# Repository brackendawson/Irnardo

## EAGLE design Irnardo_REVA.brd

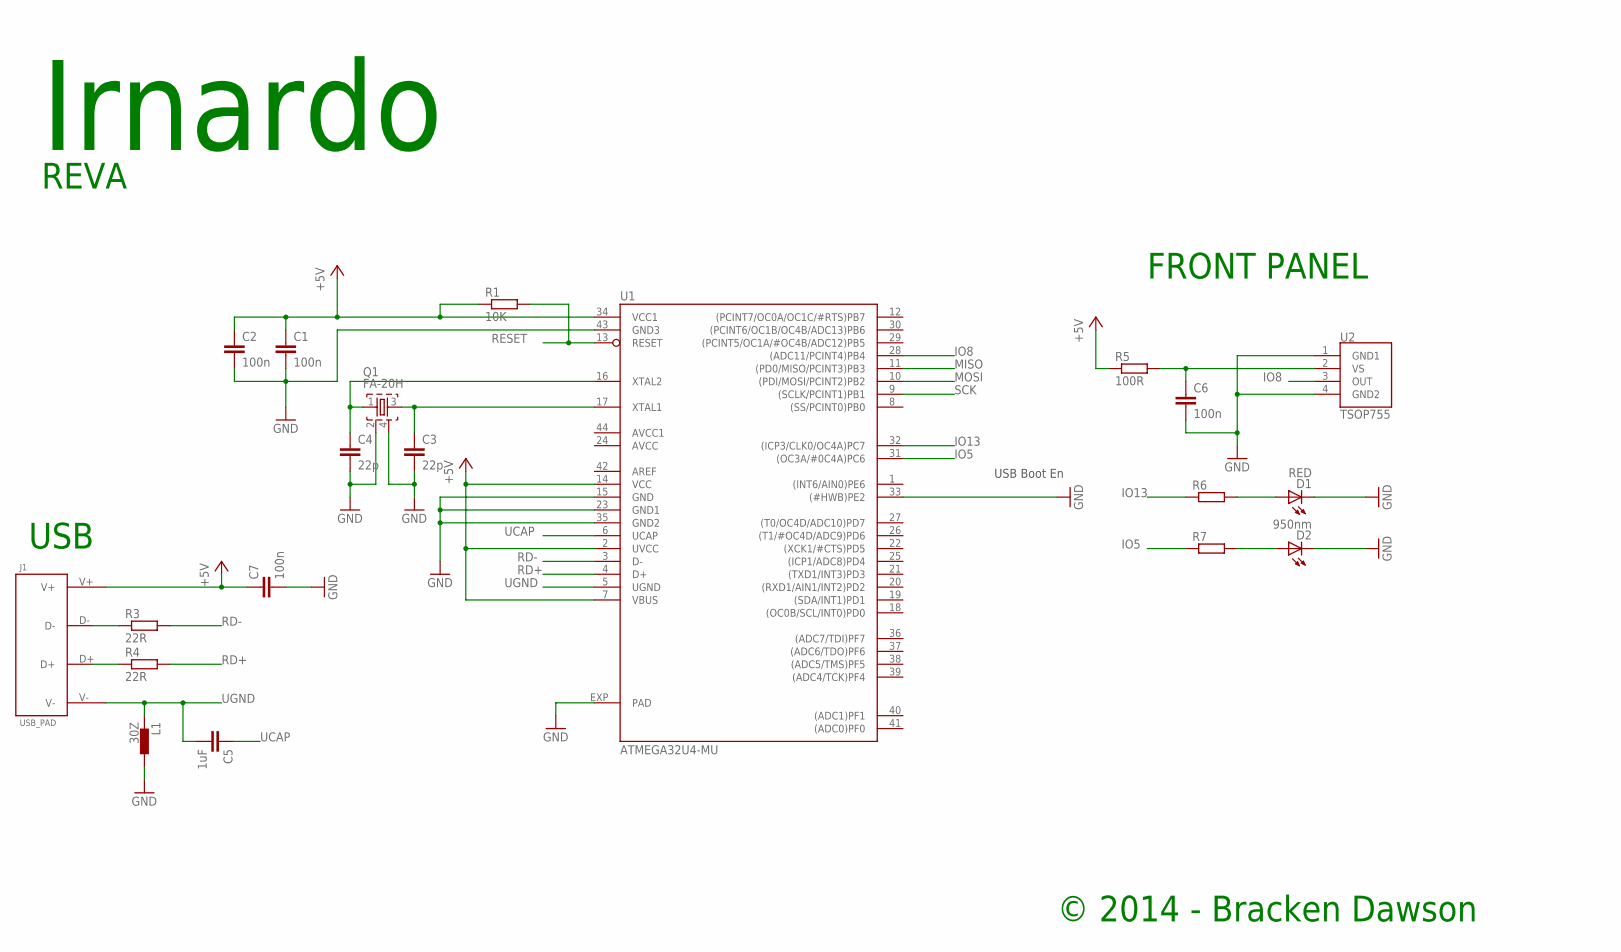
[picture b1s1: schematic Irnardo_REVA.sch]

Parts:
C1, C2, C6, C7: 100n; C0402
C3, C4: 22p; C0402
C5: 1uF; C0402
D1: RED; SML0603
D2: 950nm; SML0603
J1: USB_PAD
L1: 30Z; 0402
Q1: FA-20H
R1: 10K; R0402
R3, R4: 22R; R0402
R5: 100R; R0402
R6, R7: R-EU_R0402; R0402
U1: ATMEGA32U4-MU; SMARTPRJ_QFN44ML7X7
U2: TSOP755

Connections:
+5V: C1.1, C2.1, C7.1, J1.V+, R1.1, R5.1, U1.2 (UVCC), U1.7 (VBUS), U1.14 (VCC), U1.34 (VCC1)
AREF: U1.42 (AREF)
AVCC: U1.24 (AVCC)
AVCC1: U1.44 (AVCC1)
D+: J1.D+, R4.1
D-: J1.D-, R3.1
GND: C1.2, C2.2, C3.2, C4.2, C6.2, C7.2, D1.C, D2.C, L1.2, Q1.2, Q1.4, U1.15 (GND), U1.23 (GND1), U1.33 ((#HWB)PE2), U1.35 (GND2), U1.43 (GND3), U1.EXP (PAD), U2.1 (GND1), U2.4 (GND2)
IO5: R7.1, U1.31 ((OC3A/#0C4A)PC6)
IO8: U1.28 ((ADC11/PCINT4)PB4), U2.3 (OUT)
IO13: R6.1, U1.32 ((ICP3/CLK0/OC4A)PC7)
MISO: U1.11 ((PD0/MISO/PCINT3)PB3)
MOSI: U1.10 ((PDI/MOSI/PCINT2)PB2)
unnamed: C4.1, Q1.1, U1.16 (XTAL2)
unnamed: C3.1, Q1.3, U1.17 (XTAL1)
unnamed: C6.1, R5.2, U2.2 (VS)
unnamed: D2.A, R7.2
unnamed: D1.A, R6.2
RD+: R4.2, U1.4 (D+)
RD-: R3.2, U1.3 (D-)
RESET: R1.2, U1.13 (RESET)
SCK: U1.9 ((SCLK/PCINT1)PB1)
UCAP: C5.1, U1.6 (UCAP)
UGND: C5.2, J1.V-, L1.1, U1.5 (UGND)

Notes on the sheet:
USB
FRONT PANEL
Irnardo
USB Boot En
REVA
© 2014 - Bracken Dawson

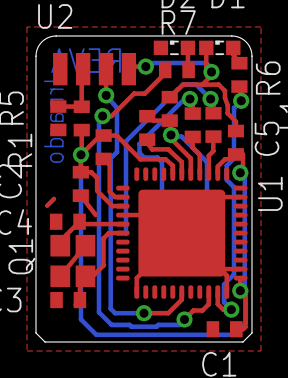
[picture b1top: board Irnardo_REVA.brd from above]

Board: 2 copper layers, 12.0 x 17.0 mm, 20 parts (1 on the bottom side), 17 nets.

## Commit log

2014-02-06 Schematic mostly done
2014-02-06 null
2014-02-06 Initial PCB design for DIY etching - incomplete
2014-02-07 Finished placing and stated wiring REVA
2014-02-08 First complete(ish) layout.
2014-02-08 Tweaks to get closer to DRC pass
2014-02-08 Fixes at hackerspace after printing and talking to
    Joel.
2014-02-09 Fix de-couple cap on IR receiver
    C6 de-coupling U2 was wrong side of R5.
2014-02-12 Swap XTAL for 2.5x2mm model
2014-02-15 Finish tweaks after move to 2.5mm XTAL
2014-02-15 Remove cream from USB pad
2014-02-15 Move a trace a little
2014-02-15 Fix DRC and dots on schematic.
2014-04-09 Expoert Gerbers
